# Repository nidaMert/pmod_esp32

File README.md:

# MuhTas-1 Project PMOD ESP32

**Overview**
---
This project focuses on the design and testing of a custom 2-layer PMOD ESP32 module, closely resembling Digilent's PMOD ESP32 product. The PMOD ESP32 module provides Wi-Fi and Bluetooth connectivity, making it an ideal choice for embedded systems and IoT applications that require wireless communication. The module is designed to interface seamlessly with microcontrollers and FPGAs via the PMOD interface, enabling rapid prototyping and testing.

The functionality of the designed PMOD ESP32 board will be verified by sending AT commands through an STM32 microcontroller.

This repository includes:
- **Hardware Design Files** for the custom PMOD ESP32 board.
- **Firmware and Documentation** for the ESP32-WROOM-32 module.
- **Testing Examples** demonstrating STM32-based communication using AT commands.

The project serves as a practical solution for developers seeking an easy-to-use wireless module for their embedded systems.

**Project Structre**
---
- **Documentation/**: Contains connection diagrams for STM32-PMOD ESP32 / PMOD ESP32-USB TTL Converter and datasheets for components.
- **Firmware/ESP32-WROOM-32-AT-V3.4.0.0/**: Includes ESP32 Wroom 32 firmware files, user guides, release notes, and other documentation related to ESP32-WROOM-32-AT V3.4.0.0.
- **Hardware Designs/**: Contains hardware design files for the PMOD ESP32 module in 2-layer and 4-layer configurations.
- **Images/**: The photos of the PMOD ESP32 module before and after soldering, as well as the photos of the completed connections, are located in this folder.
- **Library/**: The libraries of components that are necessary for the project but are not available in the KiCad library are located in this folder.
- **STM32 Applications/**: Includes STM32 Cube IDE application and logic analyzer test results.
- **.gitmodules**: Configuration file for Git submodules.
- **README.md**: This file provides an overview of the project and instructions.

**Version Comparison**
---
- Between v0.1 and v0.2 of the PCB, the only difference lies in the routing; in v0.2, the placement and number of vias were optimized to enhance signal integrity and streamline the overall layout.
- **Branch Links of Versions** :  
[PMOD_ESP32_2Layers_v0.1](https://github.com/nidaMert/pmod_esp32/tree/PMOD_ESP32_2Layers_v0.1): Initial version of the PCB.  
[PMOD_ESP32_2Layers_v0.2](https://github.com/nidaMert/pmod_esp32/tree/PMOD_ESP32_2Layers_v0.2): Updated version with optimized routing.

**Connection Diagrams**
---

**References**
---
This project was developed based on the Digilent product: [[here](https://digilent.com/reference/pmod/pmodesp32/start?redirect=1)]. The design and implementation closely resemble this product, with some modifications.

**Educational Use Only**
---
All contents of this project are shared solely for individual learning and academic evaluation. Copying, redistribution, or reuse in other projects is **strictly prohibited**.

**© Copyright**
---
**Copyright (c) 2025 Nida Mert**

All rights reserved. The source files, documentation, and visuals are provided strictly for educational and personal review purposes only.

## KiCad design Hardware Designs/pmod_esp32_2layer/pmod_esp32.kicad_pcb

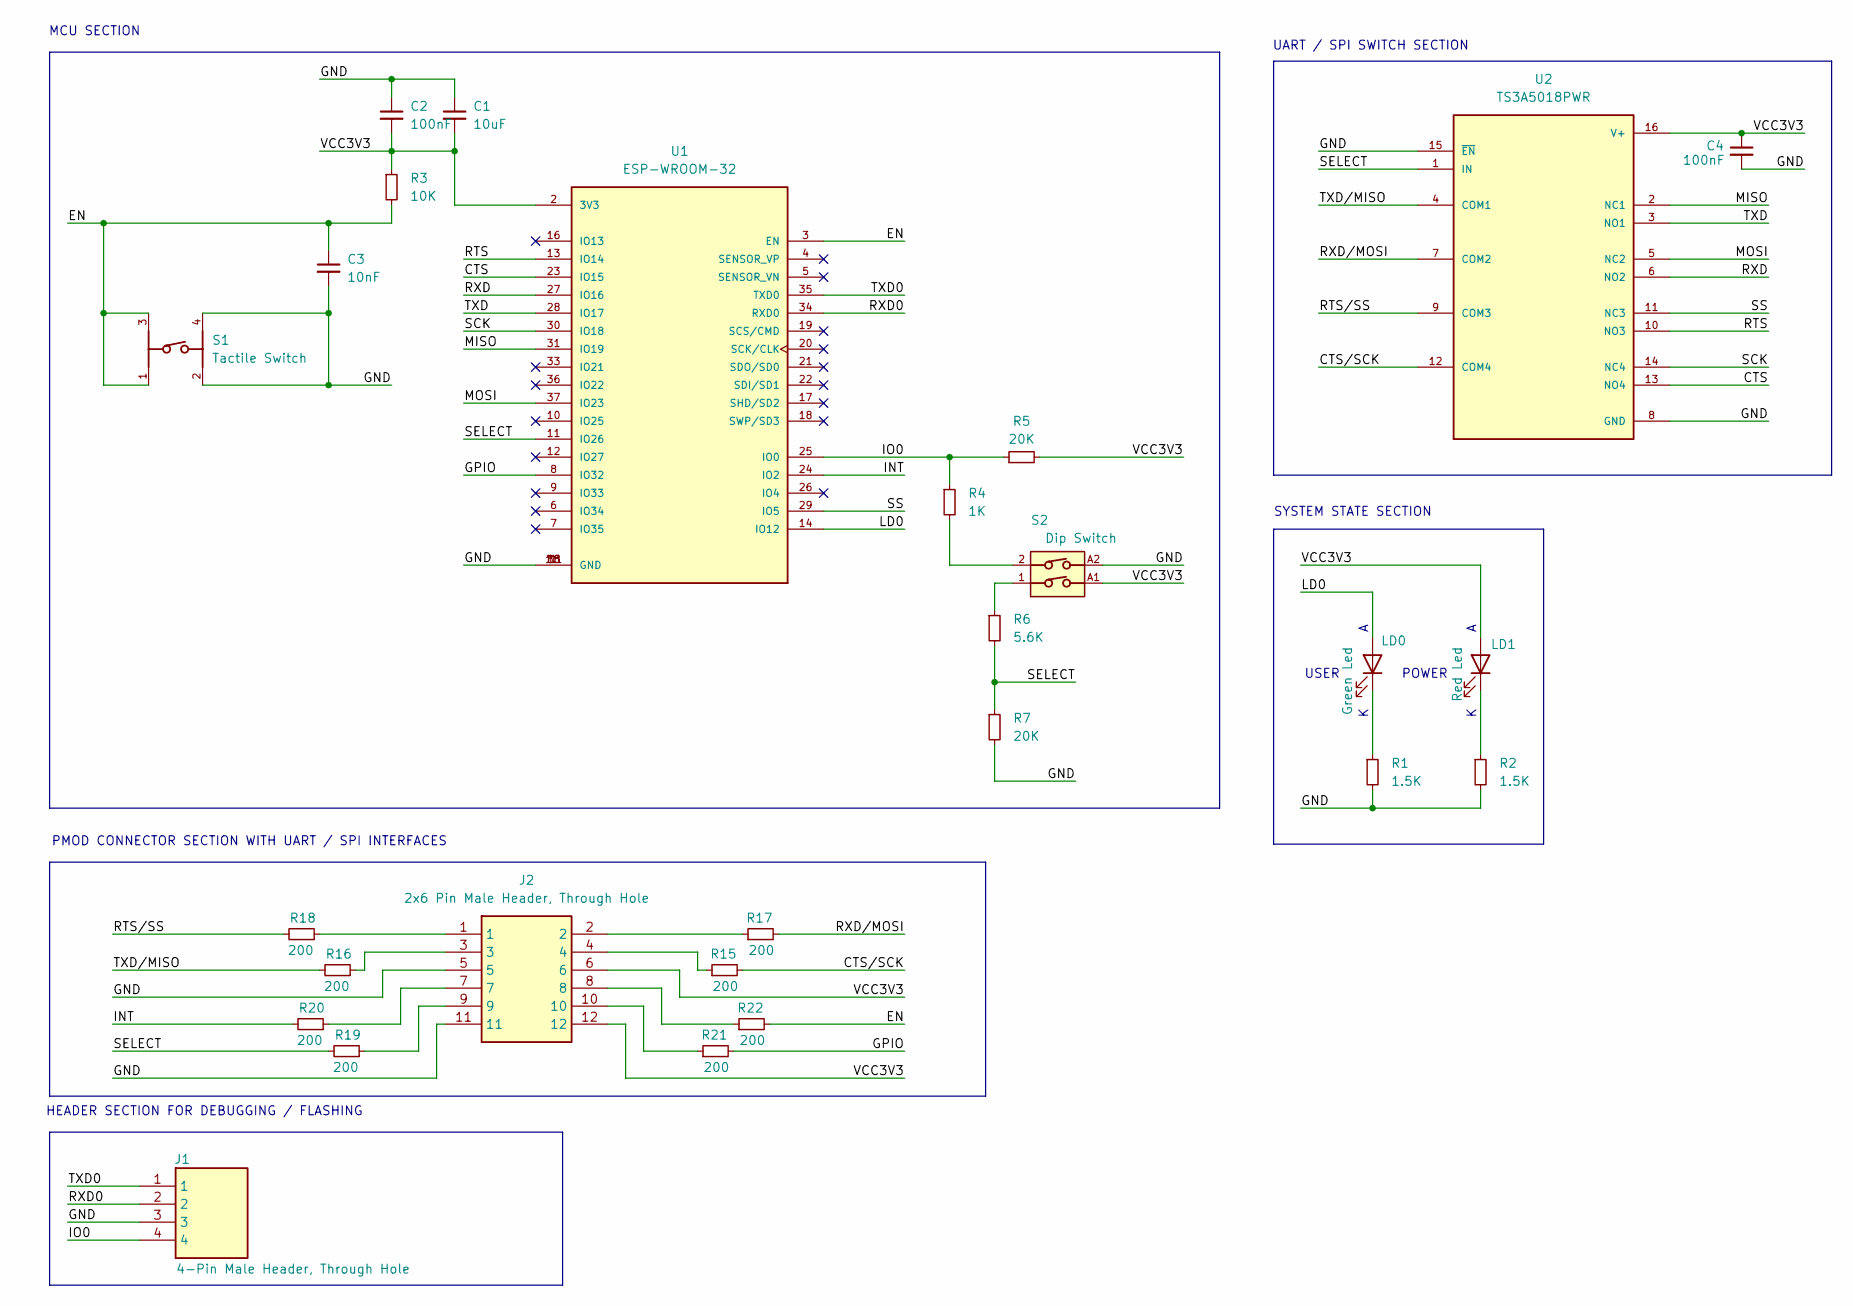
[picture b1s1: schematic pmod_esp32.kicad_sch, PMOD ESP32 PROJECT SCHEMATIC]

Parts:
C1: 10uF; C_0603_1608Metric_Pad1.08x0.95mm_HandSolder
C2, C4: 100nF; C_0603_1608Metric_Pad1.08x0.95mm_HandSolder
C3: 10nF; C_0603_1608Metric_Pad1.08x0.95mm_HandSolder
J1: 4-Pin Male Header, Through Hole; HDRV4W67P0X254_1X4_1016X241X858P; PARTREV DG
J2: 2x6 Pin Male Header, Through Hole; M209740642; Manufacturer_Part_Number M20-9740642; Mouser Part Number 855-M20-9740642
LD0: Green Led; LED_1206_3216Metric_Pad1.42x1.75mm_HandSolder
LD1: Red Led; LED_1206_3216Metric_Pad1.42x1.75mm_HandSolder
R1, R2: 1.5K; R_0603_1608Metric_Pad0.98x0.95mm_HandSolder
R3: 10K; R_0603_1608Metric_Pad0.98x0.95mm_HandSolder
R4: 1K; R_0603_1608Metric_Pad0.98x0.95mm_HandSolder
R5, R7: 20K; R_0603_1608Metric_Pad0.98x0.95mm_HandSolder
R6: 5.6K; R_0603_1608Metric_Pad0.98x0.95mm_HandSolder
R15, R16, R17, R18, R19, R20, R21, R22: 200; R_0603_1608Metric_Pad0.98x0.95mm_HandSolder
S1: Tactile Switch; 430182050816; PART-NUMBER 430182050816
S2: Dip Switch; 418121270802; PART-NUMBER 418121270802
U1: ESP-WROOM-32; MODULE_ESP-WROOM-32
U2: TS3A5018PWR; SOP65P640X120-16N; PARTREV H

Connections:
/CTS: U1.23 (IO15), U2.13 (NO4)
/CTS/SCK: R15.2, U2.12 (COM4)
/EN: C3.1, R3.2, R22.2, S1.1, S1.3, U1.3 (EN)
/GND: C1.1, C2.1, C3.2, C4.2, J1.3, J2.5, J2.11, R1.2, R2.2, R7.2, S1.2, S1.4, S2.A2, U1.1 (GND), U1.1.1 (GND), U1.15 (GND), U1.38 (GND), U2.8 (GND), U2.15 (~EN)
/GPIO: R21.2, U1.8 (IO32)
/INT: R20.2, U1.24 (IO2)
/IO0: J1.4, R4.1, R5.1, U1.25 (IO0)
/LD0: LD0.2 (A), U1.14 (IO12)
/MISO: U1.31 (IO19), U2.2 (NC1)
/MOSI: U1.37 (IO23), U2.5 (NC2)
/RTS: U1.13 (IO14), U2.10 (NO3)
/RTS/SS: R18.2, U2.9 (COM3)
/RXD: U1.27 (IO16), U2.6 (NO2)
/RXD0: J1.2, U1.34 (RXD0)
/RXD/MOSI: R17.2, U2.7 (COM2)
/SCK: U1.30 (IO18), U2.14 (NC4)
/SELECT: R6.2, R7.1, R19.2, U1.11 (IO26), U2.1 (IN)
/SS: U1.29 (IO5), U2.11 (NC3)
/TXD: U1.28 (IO17), U2.3 (NO1)
/TXD0: J1.1, U1.35 (TXD0)
/TXD/MISO: R16.2, U2.4 (COM1)
/VCC3V3: C1.2, C2.2, C4.1, J2.6, J2.12, LD1.2 (A), R3.1, R5.2, S2.A1, U1.2 (3V3), U2.16 (V+)
unnamed: J2.1, R18.1
unnamed: J2.2, R17.1
unnamed: J2.3, R16.1
unnamed: J2.4, R15.1
unnamed: J2.7, R20.1
unnamed: J2.8, R22.1
unnamed: J2.9, R19.1
unnamed: J2.10, R21.1
unnamed: LD0.1 (K), R1.1
unnamed: LD1.1 (K), R2.1
unnamed: R4.2, S2.2
unnamed: R6.1, S2.1

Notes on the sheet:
POWER
PMOD CONNECTOR SECTION WITH UART / SPI INTERFACES
SYSTEM STATE SECTION
UART / SPI SWITCH SECTION
USER
HEADER SECTION FOR DEBUGGING / FLASHING
MCU SECTION

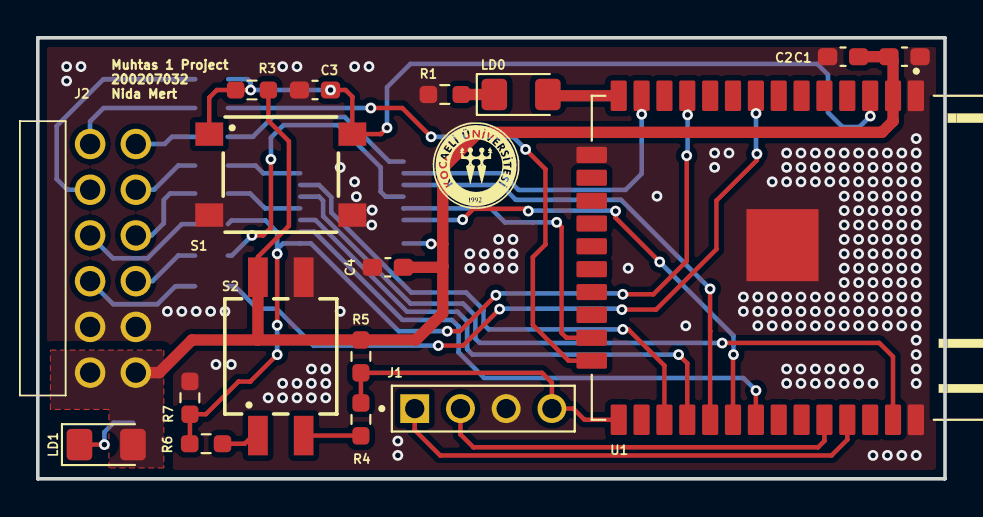
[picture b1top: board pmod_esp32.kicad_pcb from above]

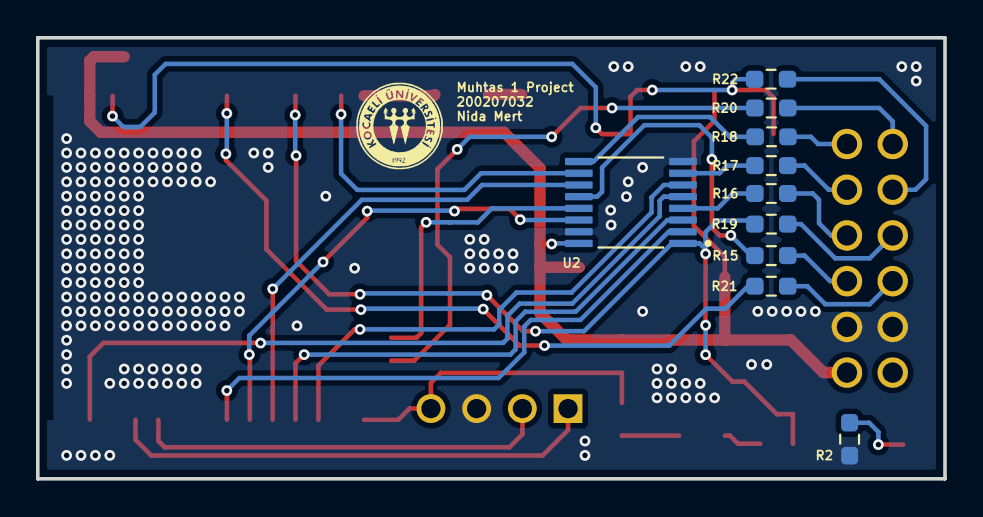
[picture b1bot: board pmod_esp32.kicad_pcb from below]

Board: 2 copper layers, 50.4 x 24.5 mm, 27 parts (10 on the bottom side), 34 nets.

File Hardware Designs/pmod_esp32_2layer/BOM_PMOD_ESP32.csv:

Reference,Value,Datasheet,Qty,MANUFACTURER,PACKAGE,Price,Description,
C1,10uF,https://cdn.ozdisan.com/ETicaret_Dosya/1078246_1413433342..pdf,1,Viking,603,0.23 TL,"Unpolarized capacitor, small symbol",
"C2,C4,C5",100nF,https://www.mouser.com.tr/datasheet/2/585/MLCC-1837944.pdf,3,Samsung,603,0.21 TL,"Unpolarized capacitor, small symbol",
C3,10nF,https://www.mouser.com.tr/datasheet/2/585/MLCC_Automotive-18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,1,Samsung,603,0.14 TL,"Unpolarized capacitor, small symbol",
J1,"4-Pin Male Header, THT",https://pdf.direnc.net/upload/5-pin-1x5-2-54mm-erkek-pin-hea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,1,Connfly,,6.59 TL,"5-Pin Single Row Male Header, 2.54mm Pitch, Through-Hole Mount",
J2,"2x6 Pin Male Header, THT",https://pdf.direnc.net/upload/20-pin-2x10-2-54mm-erkek-pin-h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,1,Connfly,,5.99 TL,"2.54mm (0.1"") Pitch DIL Horizontal Throughboard Pin Header, 5.8mm mating pin height, selective gold + tin, 6+6 contacts",
LD0,Green Led,https://pdf.direnc.net/upload/dstk6802-datasheet.pdf,1,Honglitronic,1206,0.81 TL,Light emitting diode (green led),
LD1,Red Led,https://pdf.direnc.net/upload/dstk6799-datasheet.pdf,1,Honglitronic,1206,0.94 TL,Light emitting diode (red led),
"R1,R2",1.5K,https://cdn.ozdisan.com/ETicaret_Dosya/399380_9872459.pdf,2,ROYALOHM,603,0.00032 TL,1.5K Resistor,
R3,10K,https://cdn.ozdisan.com/ETicaret_Dosya/399380_9872459.pdf,1,ROYALOHM,603,0.06 TL,10K Resistor,
R4,1K,https://cdn.ozdisan.com/ETicaret_Dosya/399380_9872459.pdf,1,ROYALOHM,603,0.06 TL,1K Resistor,
"R5,R7",20K,https://cdn.ozdisan.com/ETicaret_Dosya/399380_9872459.pdf,2,ROYALOHM,603,0.06 TL,20K Resistor,
R6,5.6K,https://cdn.ozdisan.com/ETicaret_Dosya/399380_9872459.pdf,1,ROYALOHM,603,0.00032 TL,5.6K Resistor,
"R15,R16,R17,R18,R19,R20,R21,R22",200,https://cdn.ozdisan.com/ETicaret_Dosya/399380_9872459.pdf,8,ROYALOHM,603,0.05 TL,200 Ohm Resistor,
S1,Tactile Switch,https://www.we-online.com/components/products/datasheet/4301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,1,Würth,,25.85 TL,SWITCH TACTILE SPST-NO 0.05A 12V,
S2,Dip Switch,https://cdn.ozdisan.com/ETicaret_Dosya/649724_1913908935..pdf,1,Würth,,65.07 TL,SWITCH DIP 2 WAY BLACK SMT V/T,
"S3,S4",SPDT Analog Switch,https://www.ti.com/lit/ds/symlink/ts5a23157.pdf?HQS=dis-dk-n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,2,Texas Instruments,,24.86 TL,IC SWITCH SPDT X 2 10OHM 10VSSOP,
U1,ESP-WROOM-32,https://www.mouser.com/datasheet/2/891/esp-wroom-32_datashee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,1,Espressif Systems,,125.56 TL,ESP-WROOM-32 4Mbit Flash WiFi ve Bluetooth Modül,

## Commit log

2024-12-03 stm32 first commit
2024-12-03 at firmware added
2024-12-12 Some issues have been resolved
2024-12-13 Submodule reference updated
2024-12-23 The final versions of the PCB designs have been added.
2024-12-23 The project has been updated to its final version.
2024-12-24 The folders have been organized.
2024-12-24 The Library folder has been updated in the main repository.
2024-12-24 Added version 0.1 PMOD ESP32 2 Layer
2024-12-24 Added version 0.2 PMOD ESP32 2 Layer
2024-12-24 Prevent fast-forward merge.
2024-12-24 Created a new README file.
2024-12-30 readme test
2024-12-30 Edit1 README.md
2024-12-30 images folder have been added, and made some changes in STM32 Applications folder
2024-12-30 readme file added
2024-12-30 image test on readme file
2024-12-30 The readme.md file has been updated.
2024-12-30 The readme.md file has been updated to its final version.
2024-12-31 version comparison have been added to RAEADME.md file
2024-12-31 branch links of PCB versions have been added.
2025-05-16 Final github update README.md
